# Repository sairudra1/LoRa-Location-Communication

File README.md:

# 📡 LoRa Location Communication System

**Solution for SIH 2025**  
**Problem Statement ID:** 25255  

A low-power, long-range **LoRa-based location and communication system** designed using **ESP32 and SX1278**, with a mobile application interface built using **MIT App Inventor**.

## 🧩 Key Features

- 📡 Long-range LoRa communication
- 🔋 Low-power system design
- 📍 Location-based data transmission
- 📱 Android app interface
- 🛠️ Custom PCB design
- 🔄 Reliable peer-to-peer communication

## 🛠️ Tech Stack

### Hardware
- ESP32 Dev Board
- LoRa SX1278 Module
- Custom PCB
- 16x2 LCD Display
- Buttons

### Software
- Arduino IDE (ESP32 firmware)
- MIT App Inventor (Android App)
- draw.io (Block Diagrams)
Structure

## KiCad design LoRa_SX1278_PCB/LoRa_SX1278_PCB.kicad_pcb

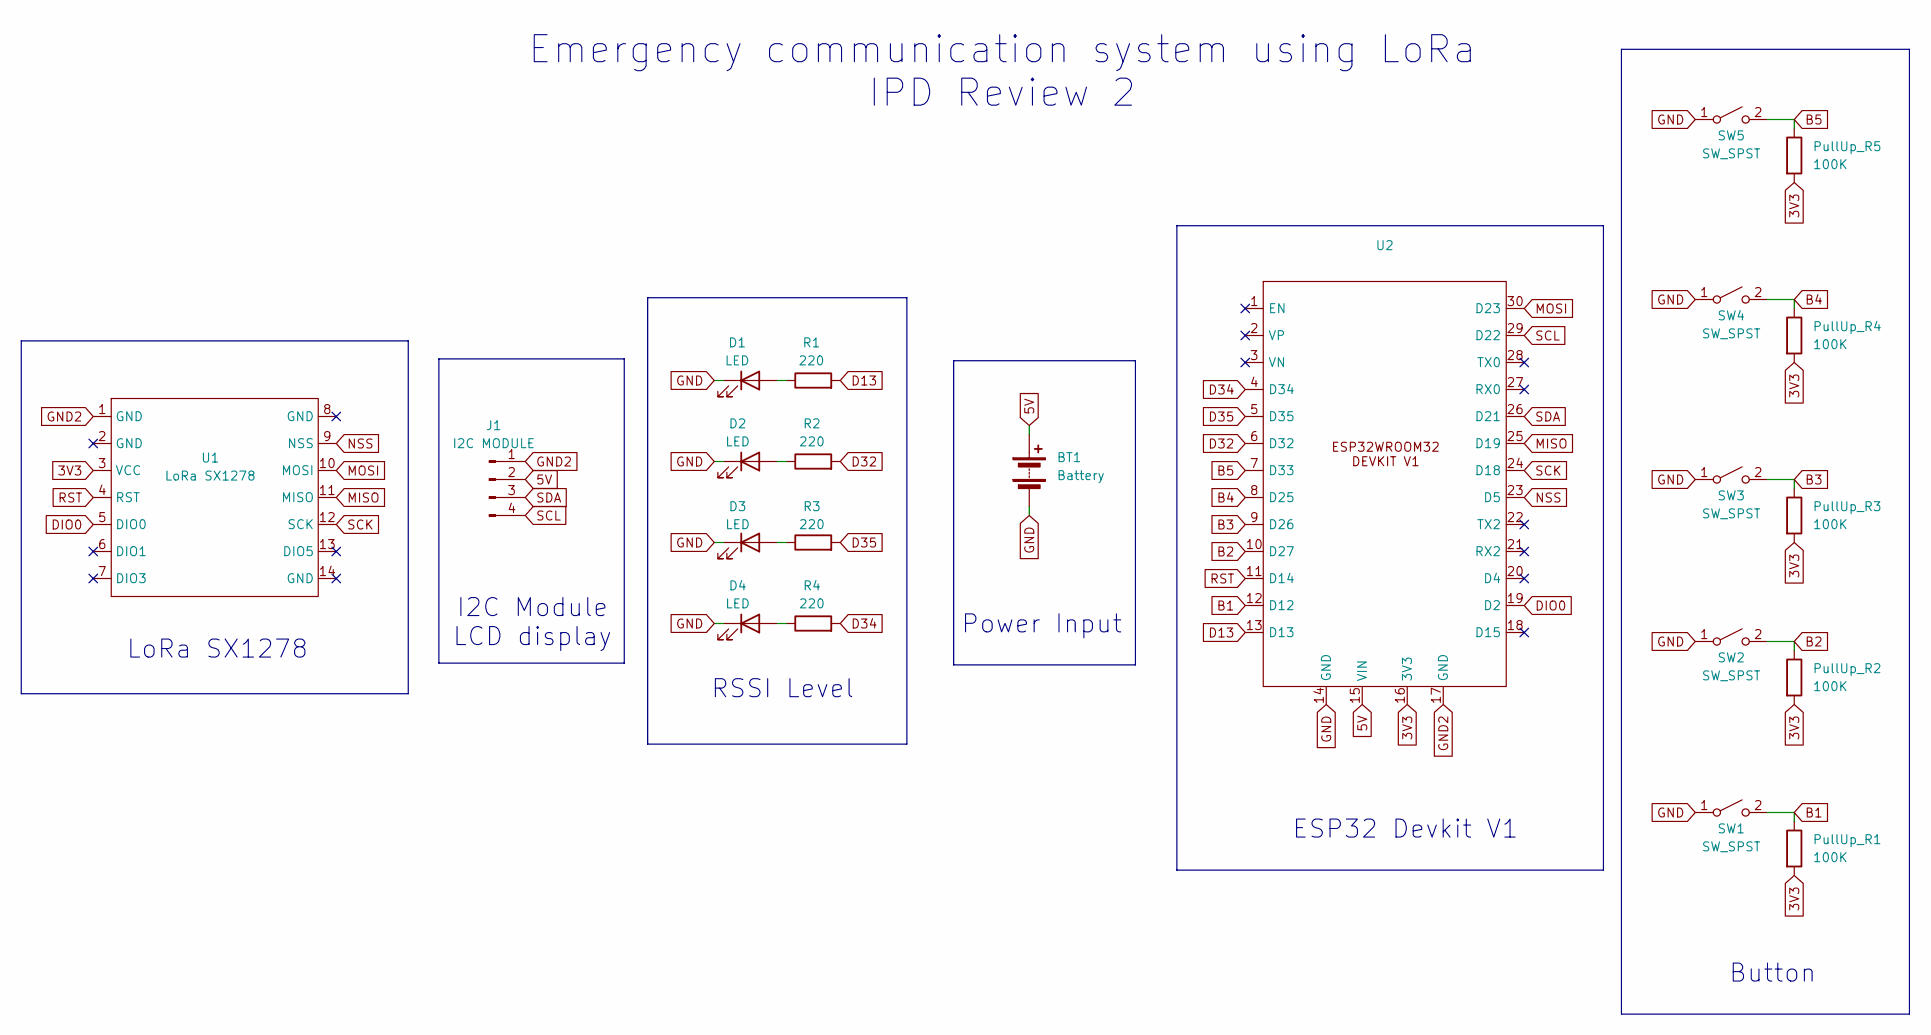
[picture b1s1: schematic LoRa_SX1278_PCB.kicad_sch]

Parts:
BT1: Battery; PinHeader_1x02_P2.54mm_Vertical
D1, D2, D3, D4: LED; LED_D3.0mm_Horizontal_O3.81mm_Z2.0mm
J1: I2C MODULE; PinHeader_1x04_P2.54mm_Vertical
PullUp_R1, PullUp_R2, PullUp_R3, PullUp_R4, PullUp_R5: 100K; R_Axial_DIN0204_L3.6mm_D1.6mm_P7.62mm_Horizontal
R1, R2, R3, R4: 220; R_Axial_DIN0204_L3.6mm_D1.6mm_P7.62mm_Horizontal
SW1, SW2, SW3, SW4, SW5: SW_SPST; SW_TH_Tactile_Omron_B3F-100x
U1: LoRa SX1278; LoRa_SX1278
U2: ESP32DEVIKITV1

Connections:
3V3: PullUp_R1.2, PullUp_R2.2, PullUp_R3.2, PullUp_R4.2, PullUp_R5.2, U1.3 (VCC), U2.16 (3V3)
5V: BT1.1 (+), J1.2, U2.15 (VIN)
B1: PullUp_R1.1, SW1.2 (B), U2.12 (D12)
B2: PullUp_R2.1, SW2.2 (B), U2.10 (D27)
B3: PullUp_R3.1, SW3.2 (B), U2.9 (D26)
B4: PullUp_R4.1, SW4.2 (B), U2.8 (D25)
B5: PullUp_R5.1, SW5.2 (B), U2.7 (D33)
D13: R1.2, U2.13 (D13)
D32: R2.2, U2.6 (D32)
D34: R4.2, U2.4 (D34)
D35: R3.2, U2.5 (D35)
DIO0: U1.5 (DIO0), U2.19 (D2)
GND: BT1.2 (-), D1.1 (K), D2.1 (K), D3.1 (K), D4.1 (K), SW1.1 (A), SW2.1 (A), SW3.1 (A), SW4.1 (A), SW5.1 (A), U2.14 (GND)
GND2: J1.1, U1.1 (GND), U2.17 (GND)
MISO: U1.11 (MISO), U2.25 (D19)
MOSI: U1.10 (MOSI), U2.30 (D23)
NSS: U1.9 (NSS), U2.23 (D5)
unnamed: D1.2 (A), R1.1
unnamed: D2.2 (A), R2.1
unnamed: D3.2 (A), R3.1
unnamed: D4.2 (A), R4.1
RST: U1.4 (RST), U2.11 (D14)
SCK: U1.12 (SCK), U2.24 (D18)
SCL: J1.4, U2.29 (D22)
SDA: J1.3, U2.26 (D21)

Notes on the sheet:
Emergency communication system using LoRa IPD Review 2
LoRa SX1278
ESP32 Devkit V1
Power Input
RSSI Level
Button
I2C Module LCD display

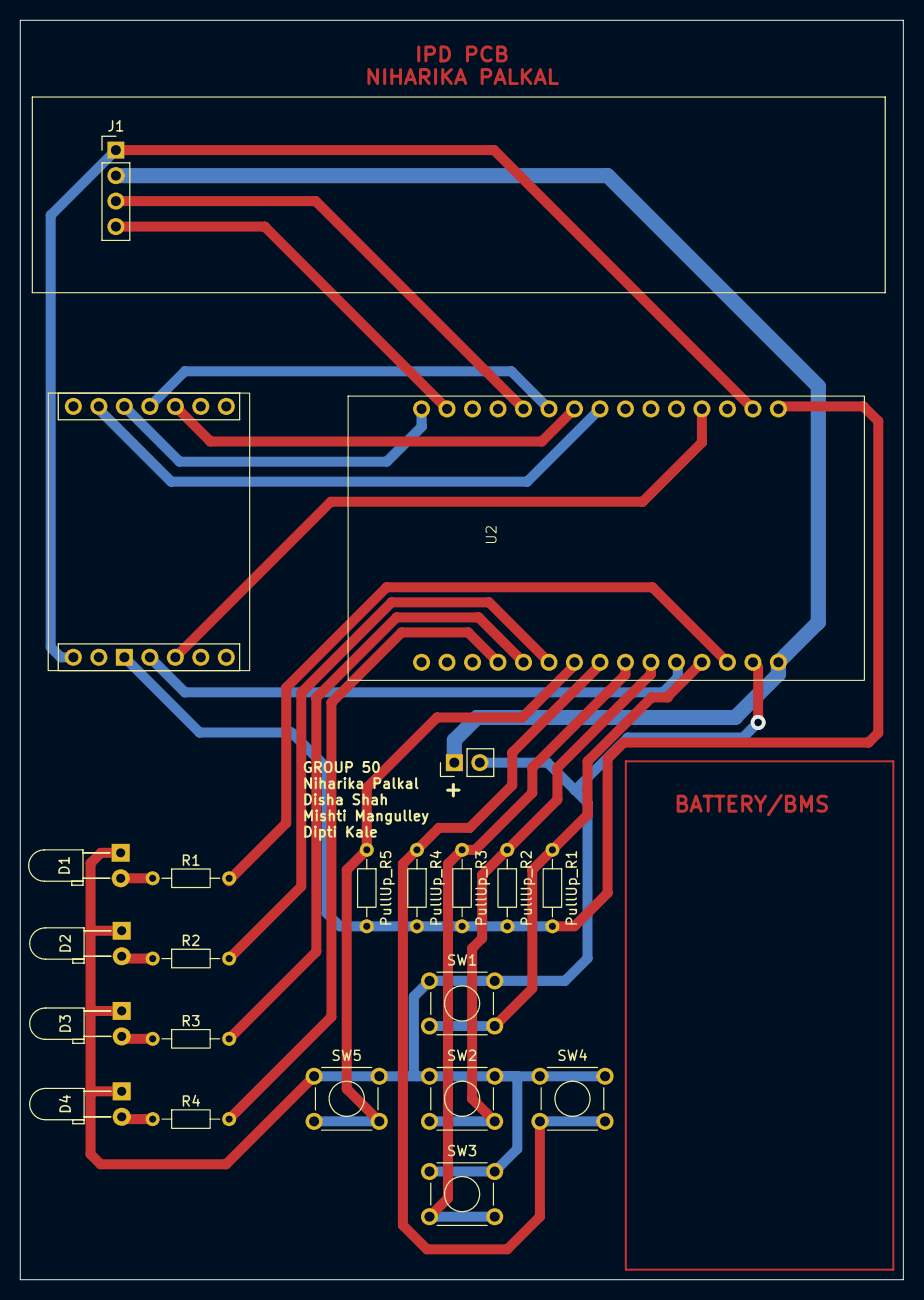
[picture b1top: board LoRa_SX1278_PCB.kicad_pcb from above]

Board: 2 copper layers, 88.0 x 125.5 mm, 22 parts (0 on the bottom side), 25 nets.

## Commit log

2025-12-24 PCB Files
2025-12-24 block diagrams
2025-12-24 MIT app inventor file
2025-12-24 ESP32 Code
